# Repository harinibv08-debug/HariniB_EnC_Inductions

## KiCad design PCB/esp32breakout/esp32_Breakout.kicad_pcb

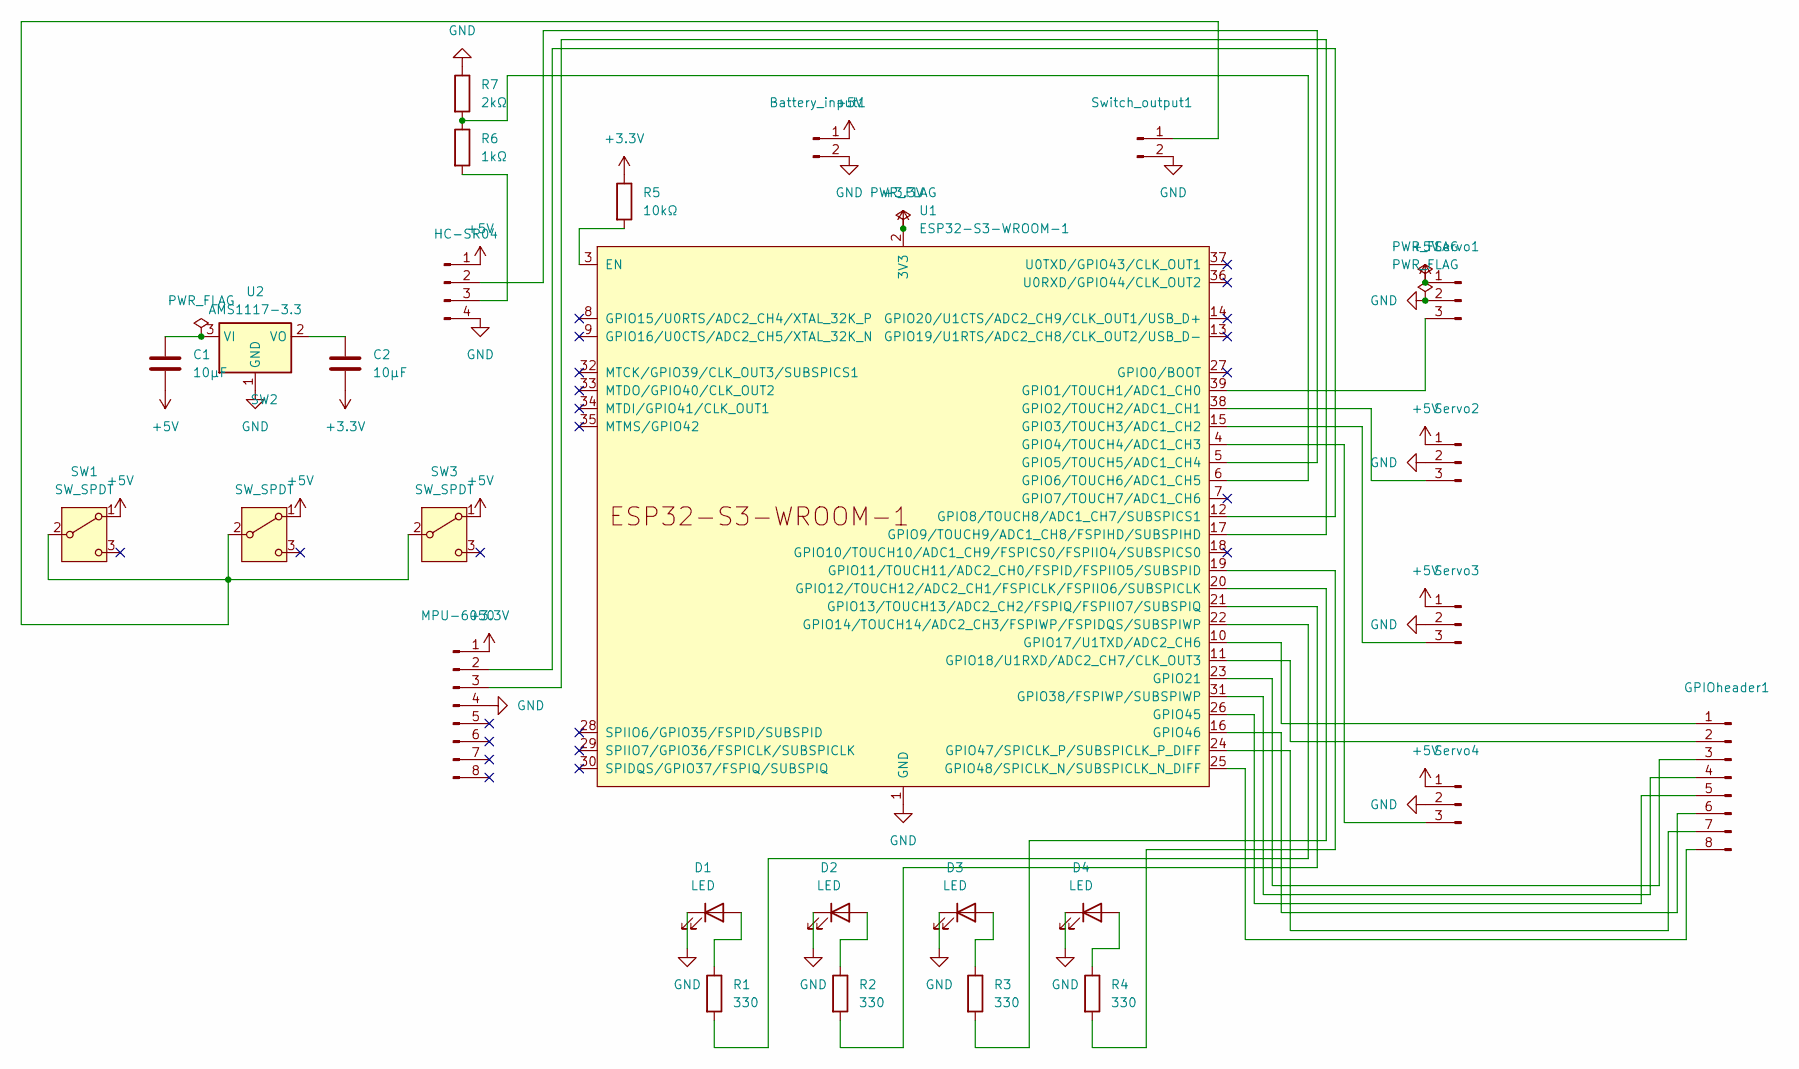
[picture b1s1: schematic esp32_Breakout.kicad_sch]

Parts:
Battery_input1: PinHeader_1x02_P2.54mm_Vertical
C1, C2: 10µF; C_Disc_D5.0mm_W2.5mm_P5.00mm
D1, D2, D3, D4: LED; LED_D5.0mm
GPIOheader1: PinHeader_1x08_P2.54mm_Vertical
HC-SR04: PinHeader_1x04_P2.54mm_Vertical
MPU-6050: PinHeader_1x08_P2.54mm_Vertical
R1, R2, R3, R4: 330; R_Axial_DIN0207_L6.3mm_D2.5mm_P10.16mm_Horizontal
R5: 10kΩ; R_Axial_DIN0207_L6.3mm_D2.5mm_P10.16mm_Horizontal
R6: 1kΩ; R_Axial_DIN0207_L6.3mm_D2.5mm_P10.16mm_Horizontal
R7: 2kΩ; R_Axial_DIN0207_L6.3mm_D2.5mm_P10.16mm_Horizontal
SW1, SW2, SW3: SW_SPDT; SW_E-Switch_EG1224_SPDT_Angled
Servo1, Servo2, Servo3, Servo4: PinHeader_1x03_P2.54mm_Vertical
Switch_output1: PinHeader_1x02_P2.54mm_Vertical
U1: ESP32-S3-WROOM-1
U2: AMS1117-3.3; SOT-223-3_TabPin2

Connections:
+3.3V: C2.2, MPU-6050.1, R5.1, U1.2 (3V3)
+5V: Battery_input1.1, C1.2, HC-SR04.1, SW1.1 (A), SW2.1 (A), SW3.1 (A), Servo1.1, Servo2.1, Servo3.1, Servo4.1
GND: Battery_input1.2, D1.1 (K), D2.1 (K), D3.1 (K), D4.1 (K), HC-SR04.4, MPU-6050.4, R7.1, Servo1.2, Servo2.2, Servo3.2, Servo4.2, Switch_output1.2, U1.1 (GND), U1.40 (GND), U1.41 (GND), U2.1 (GND)
unnamed: D1.2 (A), R1.1
unnamed: D2.2 (A), R2.1
unnamed: D3.2 (A), R3.1
unnamed: D4.2 (A), R4.1
unnamed: GPIOheader1.1, U1.10 (GPIO17/U1TXD/ADC2_CH6)
unnamed: GPIOheader1.2, U1.11 (GPIO18/U1RXD/ADC2_CH7/CLK_OUT3)
unnamed: GPIOheader1.3, U1.23 (GPIO21)
unnamed: GPIOheader1.4, U1.31 (GPIO38/FSPIWP/SUBSPIWP)
unnamed: GPIOheader1.5, U1.26 (GPIO45)
unnamed: GPIOheader1.6, U1.16 (GPIO46)
unnamed: GPIOheader1.7, U1.24 (GPIO47/SPICLK_P/SUBSPICLK_P_DIFF)
unnamed: GPIOheader1.8, U1.25 (GPIO48/SPICLK_N/SUBSPICLK_N_DIFF)
unnamed: HC-SR04.2, U1.5 (GPIO5/TOUCH5/ADC1_CH4)
unnamed: HC-SR04.3, R6.2
unnamed: MPU-6050.2, U1.12 (GPIO8/TOUCH8/ADC1_CH7/SUBSPICS1)
unnamed: MPU-6050.3, U1.17 (GPIO9/TOUCH9/ADC1_CH8/FSPIHD/SUBSPIHD)
unnamed: SW1.2 (B), SW2.2 (B), SW3.2 (B), Switch_output1.1
unnamed: Servo1.3, U1.39 (GPIO1/TOUCH1/ADC1_CH0)
unnamed: Servo2.3, U1.38 (GPIO2/TOUCH2/ADC1_CH1)
unnamed: Servo3.3, U1.15 (GPIO3/TOUCH3/ADC1_CH2)
unnamed: Servo4.3, U1.4 (GPIO4/TOUCH4/ADC1_CH3)
unnamed: R5.2, U1.3 (EN)
unnamed: R6.1, R7.2, U1.6 (GPIO6/TOUCH6/ADC1_CH5)
unnamed: R4.2, U1.19 (GPIO11/TOUCH11/ADC2_CH0/FSPID/FSPIIO5/S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)
unnamed: R3.2, U1.20 (GPIO12/TOUCH12/ADC2_CH1/FSPICLK/FSPIIO6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)
unnamed: R2.2, U1.21 (GPIO13/TOUCH13/ADC2_CH2/FSPIQ/FSPIIO7/S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)
unnamed: R1.2, U1.22 (GPIO14/TOUCH14/ADC2_CH3/FSPIWP/FSPIDQS/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)
unnamed: C1.1, U2.3 (VI)
unnamed: C2.1, U2.2 (VO)

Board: 2 copper layers, 26 parts (0 on the bottom side), 12 nets, no tracks yet.

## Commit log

2026-06-29 Create esp32_breakout
